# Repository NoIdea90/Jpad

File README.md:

# Jpad
Is a cute lil macropad with 9 keys, 1 rotary encoder, and 1 oled screen.

# challenge
Jpad was made with exactly 0 experience in anything, coding, 3d modeling, schematics, pcb, none.
so naturally that led to me remaking the pcb about a million times from scratch, also the case
but it was definetly a fun learning experience that i gained a lot from, like how to use fusion360, make a pcb/schematic, python.

# features
An awesome design 

An OLED display that is currently very boring but i have some plans for it

9 cherry mx switches (wired in a matrix btw)

One EC11 rotary encoder with a switch

and ofc the diode window for a little ✨bedazzle✨

# BOM 
9x Cherry MX switches

9x through-hole 1N4148 Diodes

1x seeed studios xiao RP2040

1x 0.91 inch OLED display

4x M3 heatset inserts

4x M3 screws

1x EC11 Rotary encoder

# My use for it
i alt f4 alot so thats fun

# pcb!!!!!

# schematics!!!!

and this project is defo not over, i have so much more stuff i wanna do to it once i actually get my hands on it.

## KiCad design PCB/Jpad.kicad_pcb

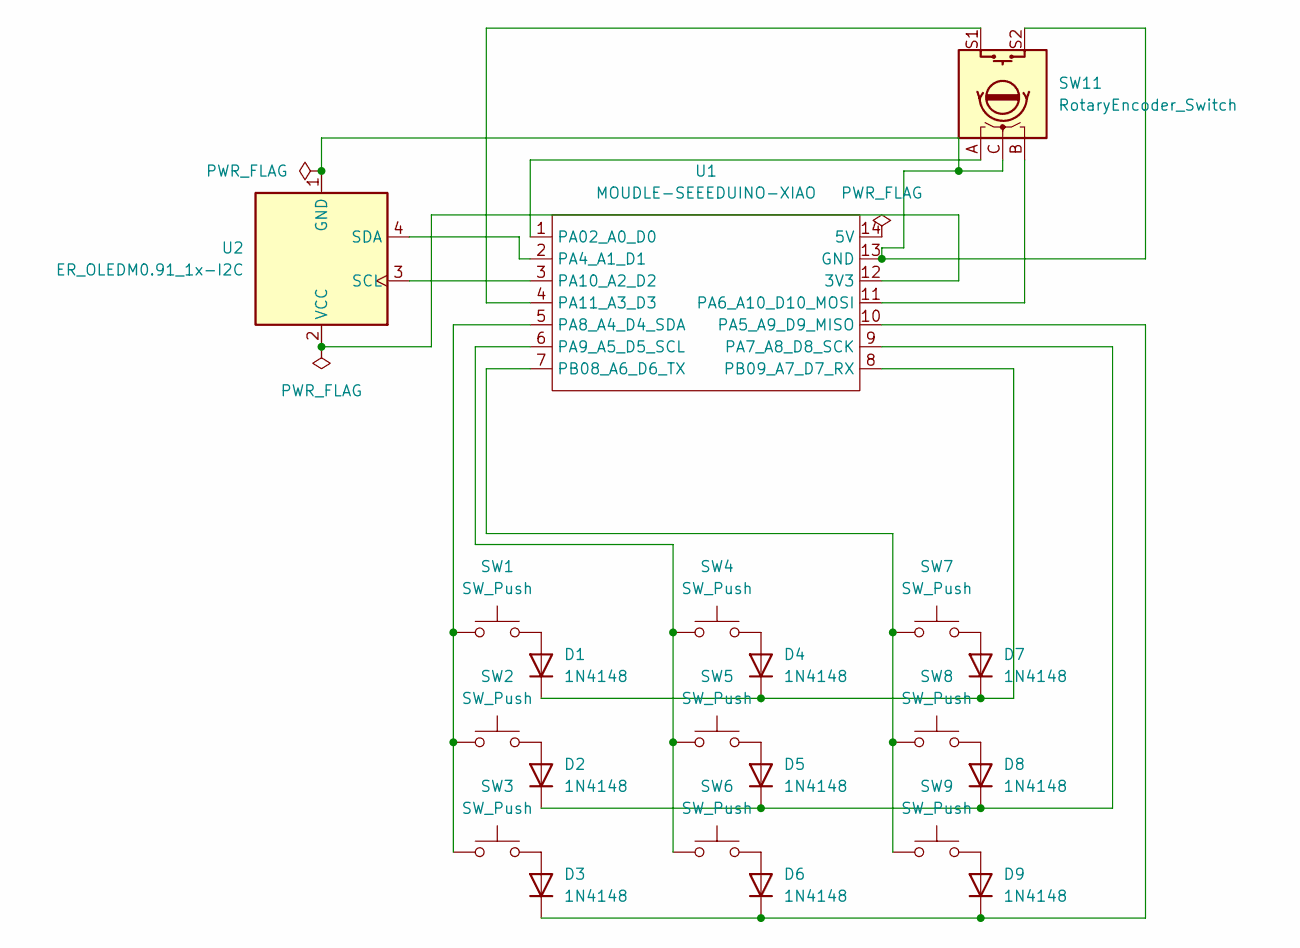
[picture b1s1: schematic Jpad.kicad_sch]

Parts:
D1, D2, D3, D4, D5, D6, D7, D8, D9: 1N4148; D_DO-35_SOD27_P7.62mm_Horizontal
SW1, SW2, SW3, SW4, SW5, SW6, SW7, SW8, SW9: SW_Push; SW_Cherry_MX_1.00u_PCB
SW11: RotaryEncoder_Switch; RotaryEncoder_Alps_EC11E-Switch_Vertical_H20mm
U1: MOUDLE-SEEEDUINO-XIAO; XIAO-Generic-Hybrid-14P-2.54-21X17.8MM
U2: ER_OLEDM0.91_1x-I2C

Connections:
unnamed: D1.2 (A), SW1.2
unnamed: D1.1 (K), D4.1 (K), D7.1 (K), U1.8 (PB09_A7_D7_RX)
unnamed: D2.2 (A), SW2.2
unnamed: D2.1 (K), D5.1 (K), D8.1 (K), U1.9 (PA7_A8_D8_SCK)
unnamed: D3.2 (A), SW3.2
unnamed: D3.1 (K), D6.1 (K), D9.1 (K), U1.10 (PA5_A9_D9_MISO)
unnamed: D4.2 (A), SW4.2
unnamed: D5.2 (A), SW5.2
unnamed: D6.2 (A), SW6.2
unnamed: D7.2 (A), SW7.2
unnamed: D8.2 (A), SW8.2
unnamed: D9.2 (A), SW9.2
unnamed: U1.12 (3V3), U2.2 (VCC)
unnamed: SW11.C, SW11.S2, U1.13 (GND), U2.1 (GND)
unnamed: SW11.A, U1.1 (PA02_A0_D0)
unnamed: U1.2 (PA4_A1_D1), U2.4 (SDA)
unnamed: SW11.B, U1.11 (PA6_A10_D10_MOSI)
unnamed: SW1.1, SW2.1, SW3.1, U1.5 (PA8_A4_D4_SDA)
unnamed: SW4.1, SW5.1, SW6.1, U1.6 (PA9_A5_D5_SCL)
unnamed: U1.3 (PA10_A2_D2), U2.3 (SCL)
unnamed: SW11.S1, U1.4 (PA11_A3_D3)
unnamed: SW7.1, SW8.1, SW9.1, U1.7 (PB08_A6_D6_TX)

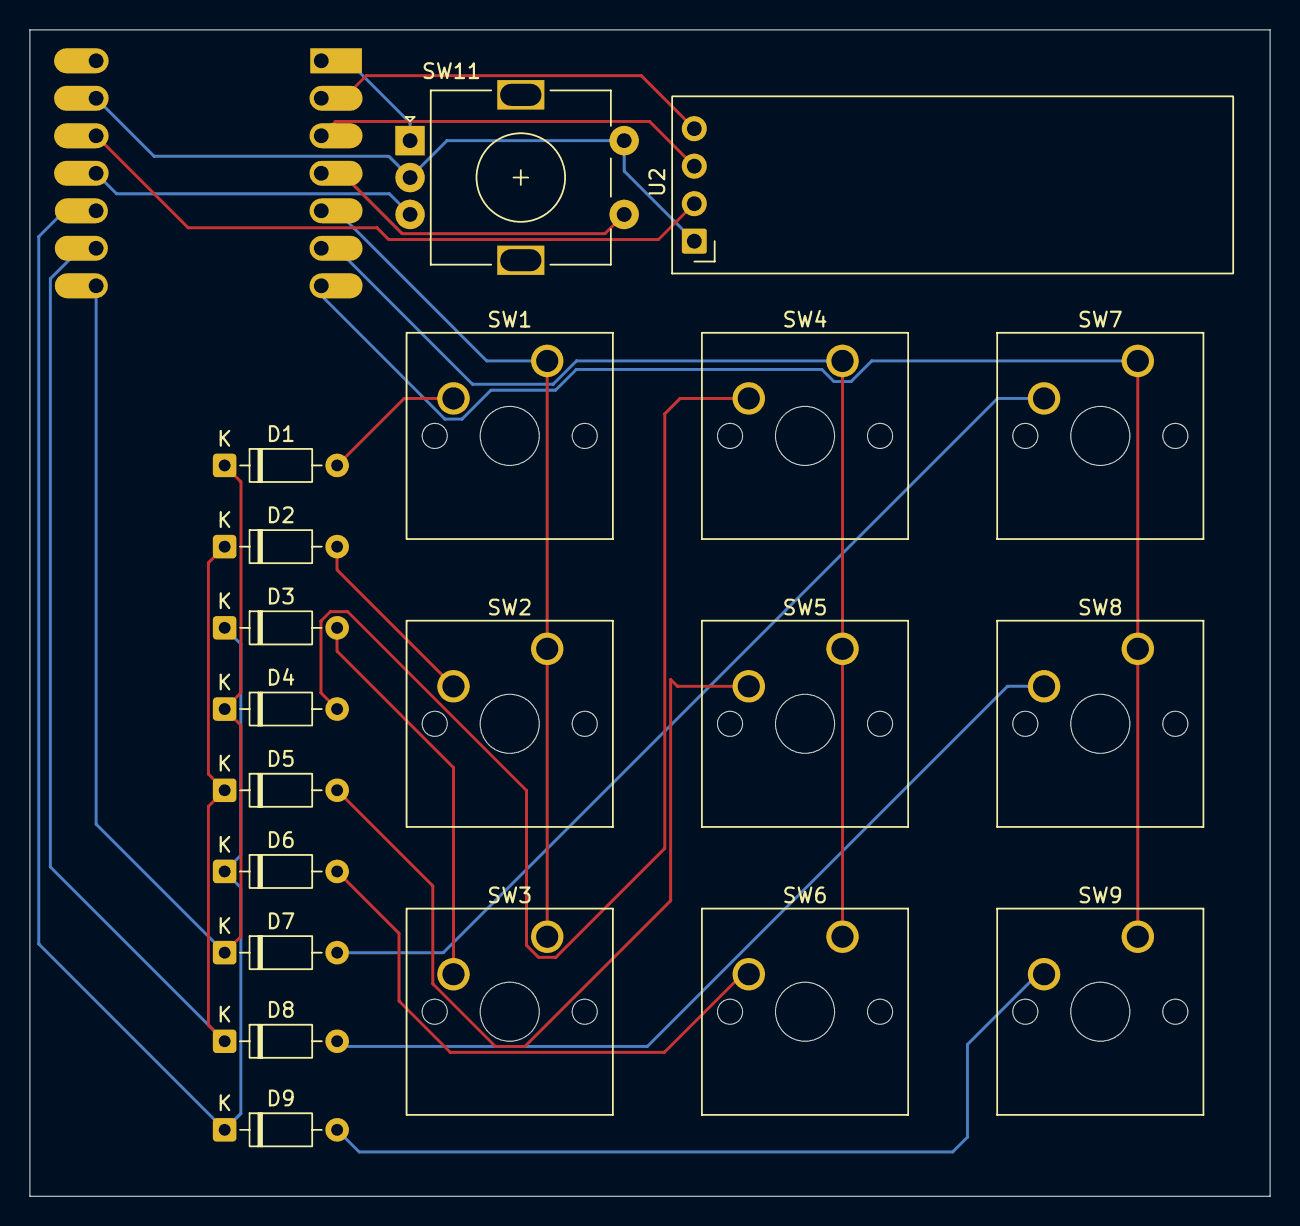
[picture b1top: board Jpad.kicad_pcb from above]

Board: 2 copper layers, 84.0 x 79.0 mm, 21 parts (1 on the bottom side), 22 nets.

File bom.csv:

Designator,Footprint,Quantity,Value,LCSC Part #
"D1, D2, D3, D4, D5, D6, D7, D8, D9",D_DO-35_SOD27_P7.62mm_Horizontal,9,1N4148,
"SW1, SW2, SW3, SW4, SW5, SW6, SW7, SW8, SW9",SW_Cherry_MX_1.00u_PCB,9,SW_Push,
SW11,RotaryEncoder_Alps_EC11E-Switch_Vertical_H20mm,1,RotaryEncoder_Switch,
U1,XIAO-Generic-Hybrid-14P-2.54-21X17.8MM,1,MOUDLE-SEEEDUINO-XIAO,
U2,ER_OLEDM0.91_1x-I2C,1,ER_OLEDM0.91_1x-I2C,
